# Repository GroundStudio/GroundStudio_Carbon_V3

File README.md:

GroundStudio Carbon V3
====================================

Get it from [ardushop.ro](https://ardushop.ro/en/electronics/537-placa-de-dezvoltare-carbon-v3-6427854000392.html)

Explore all the GroundStudio products at [ardushop.ro](https://ardushop.ro/en/37-groundstudio)

Description
-------------------
Features ESP32 based Pico V3-02 with 2.4 GHz WiFi, V4.2 Bluetooth, 8MB SPI Flash, 2MB SPI PSRAM, 520kB internal SRAM, 448kB ROM, 18 GPIO, 12 ADC and 6 touch sensitive pins, I²C 3V3 adapter, RGB smart LED, 1 cell LiPo/LiIon battery charger with optional battery connector and CH340C for USB comunication.

Contents
-------------------

* [/Documentation](https://github.com/GroundStudio/GroundStudio_Carbon_V3/tree/main/Documentation) -- Pinout.
* [/Hardware](https://github.com/GroundStudio/GroundStudio_Carbon_V3/tree/main/Hardware) -- Schematics, layout.
* [/Arduino](https://github.com/GroundStudio/GroundStudio_Carbon_V3/tree/main/Arduino/Examples) -- Arduino test examples.

Versions
-------------------
*(Not all tags shown)*

- [REV 0.0.2]:
  - testing different uart pins setup

- [REV 0.0.3]:
  - added test point for GPIO0
  - added 100nF in parallel with R14 for better battery voltage level reading
  - adjusted the position of pin labels for better visibility

License
-------------------

This is released under the [Attribution-ShareAlike 4.0 International (CC BY-SA 4.0)](https://creativecommons.org/licenses/by-sa/4.0/) license.
**You are welcome to use this for commercial purposes.**

Please consider contributing back to this project or others to help the open-source hardware community continue to thrive and grow!

Certifications:

[Open Source Hardware Association](https://certification.oshwa.org/ro000007.html)   
   
[
](https://certification.oshwa.org/ro000007.html)

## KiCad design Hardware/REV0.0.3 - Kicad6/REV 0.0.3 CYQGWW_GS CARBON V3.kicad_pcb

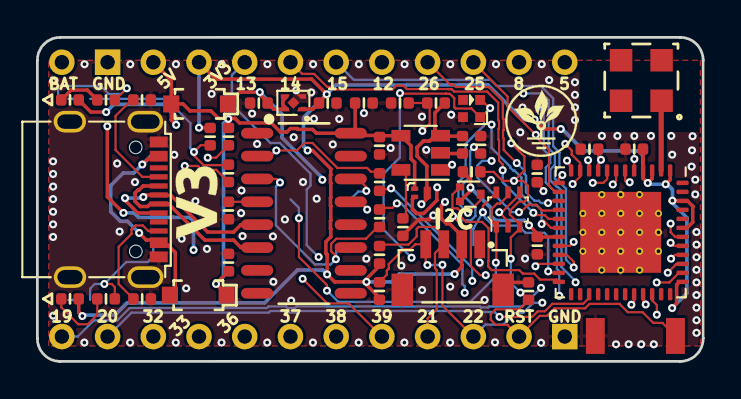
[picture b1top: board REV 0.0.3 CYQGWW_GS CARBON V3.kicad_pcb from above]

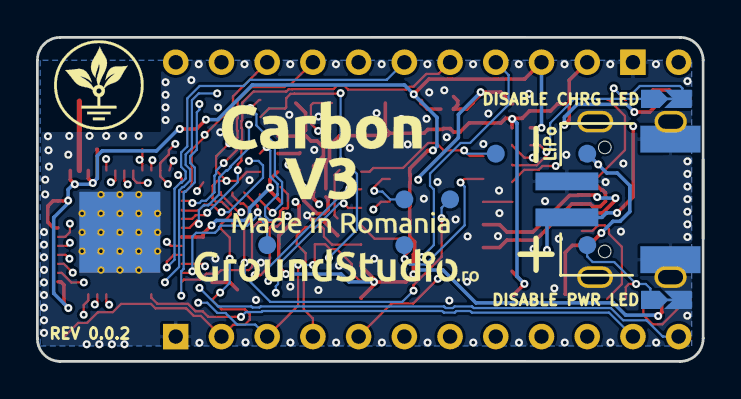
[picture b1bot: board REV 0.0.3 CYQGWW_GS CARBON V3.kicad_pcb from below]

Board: 4 copper layers, 37.0 x 18.0 mm, 56 parts (5 on the bottom side), 50 nets.

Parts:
ANT1: 2065130001
C1, C5, C6, C7, C11: C_0402_1uF_10V; C_0402_alt
C2, C9, C10: C_0402_100nF_16V; C_0402_alt
C3, C4: C_0402_10uF_10V; C_0402_alt
C8: C_0402_10nF_50V; C_0402_alt
CR1: SOD-123 B0520LW; SOD-123
D1: LED_0402_GREEN; LED_0402_alt
D3: SOD-123 B0520LW; SOD-123
IC1: SOT-23-5 BRCL4054CME; SOT-23-5
J1, J2: PinHeader_1x12_P2.54_V_M A2541WV-12P; PinHeader_1x12_P2.54mm_Vertical_Male
J4: PWR LED DISABLE; SolderJumper_NC
J7: disable CHARGING LED; SolderJumper_NC
LED2: LED_0402_RED; LED_0402_alt
LED3: SK6805-EC15 DY-S1515065; SK6805-EC15
Q1: SOT-363 MUN5214DW1T1G; SOT-363
Q2: SOT-883 LP0404N3T5G; SOT-883
R1, R2: R_0402_5.1k; R_0402_alt
R5: R_0402_100k; R_0402_alt
R6, R7, R16, R17: R_0402_3.3k; R_0402_alt
R8, R19: R_0402_2k; R_0402_alt
R9, R10, R11, R12: R_0402_1k; R_0402_alt
R13: R_0402_442k; R_0402_alt
R14: R_0402_160k; R_0402_alt
R15: R_0402_10k; R_0402_alt
R18: R_0402_820k; R_0402_alt
REG1: FBP1-1-4_ME6211C33U4AG-N; FBP1-1-4
SW1: TS342A2P-WZ
T1: SOT-723_DTA143ZMT2L; SOT-723
TP1: TP_RTS; TestPoint
TP2: IO0; TestPoint
TP3: TP_USB_VCC; TestPoint
TP5: TP_ONL; TestPoint
TP6: TP_TX; TestPoint
TP7: TP_RX; TestPoint
TP8: TP_DTR; TestPoint
U1: QFN-48-7x7mm ESP32-PICO-V3-02; QFN-48-1EP_7x7mm_P0.5mm_EP4.5x4.5mm
U2: SOP-16_150MIL CH340C; SOP-16_150MIL
USB1: USB_C 918-418K2023S40001; USB_C_C167321
X1: PH__1x02_P2.00mm_Horizontal C47647; PH__1x02_P2.00mm_Horizontal
X2: SH__1x04_Vertical C145961; SH__1x04_P1.00mm_Vertical

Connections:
+3V3: C2.1, C3.1, C6.1, J1.4, LED2.2, R15.2, R16.2, R17.1, R18.1, REG1.1, T1.2, U1.1, U1.3, U1.4, U1.19, U1.37, U1.43, U1.46, X2.2
+BAT: C4.1, IC1.3, J1.1, Q2.3, R13.2, X1.2
CH340C_RX: R12.2, TP7.~, U2.3
CH340C_TX: R11.2, TP6.~, U2.2
D+: U2.5, USB1.A6, USB1.B6
D-: U2.6, USB1.A7, USB1.B7
DTR: Q1.1, Q1.5, TP8.~, U2.13
EN: C1.1, C11.1, J2.11, Q1.3, R15.1, SW1.2, U1.9
GND: C1.2, C2.2, C3.2, C4.2, C5.1, C6.2, C7.2, C8.1, C9.2, C10.2, C11.2, IC1.2, J1.2, J2.12, J4.2, LED3.4, R1.2, R2.2, R5.1, R6.1, R8.1, R14.1, REG1.2, REG1.5, SW1.1, U1.49, U2.1, USB1.0, USB1.A1, USB1.A12, USB1.B1, USB1.B12, X1.0, X1.1, X2.0, X2.1
GPIO0: Q1.6, TP2.~, U1.23
GPIO2: LED3.1, U1.22
GPIO4: T1.1, U1.24
GPIO5: J1.12, U1.34
GPIO7: R7.1, R8.2, U1.32
GPIO8: J1.11, U1.33
GPIO12: J1.8, U1.18
GPIO13: J1.5, U1.20
GPIO14: J1.6, U1.17
GPIO15: J1.7, U1.21
GPIO19: J2.1, U1.38
GPIO20: J2.2, U1.27
GPIO21: J2.9, R16.1, U1.42, X2.3
GPIO22: J2.10, R17.2, U1.39, X2.4
GPIO25: J1.10, U1.14
GPIO26: J1.9, U1.15
GPIO27: R19.2, U1.16
GPIO32: J2.3, U1.12
GPIO33: J2.4, U1.13
unnamed: ANT1.1, U1.2
unnamed: C8.2, U2.4
unnamed: D1.1, R10.2
unnamed: IC1.5, R6.2
unnamed: J4.1, R9.2, TP5.~
unnamed: J7.2, R10.1
unnamed: LED2.1, R9.1
unnamed: LED3.2, T1.3
unnamed: R1.1, USB1.B5
unnamed: R2.1, USB1.A5
RTS: Q1.2, Q1.4, TP1.~, U2.14
RX_ESP32: R11.1, U1.40
SENS_CAPN: J2.7, U1.7
SENS_CAPP: J2.6, U1.6
SENS_VN: J2.8, U1.8
SENS_VP: J2.5, U1.5
TX_ESP32: R12.1, U1.41
USB: C7.1, C9.1, CR1.2, D1.2, D3.1, IC1.4, J1.3, Q2.1, R5.2, R7.2, U2.16
VBUS: C5.2, CR1.1, Q2.2, REG1.3, REG1.4
VBUS1*2: D3.2, TP3.~, USB1.A4, USB1.A9, USB1.B4, USB1.B9
VDET_2: C10.1, R13.1, R14.2, U1.11
~CHRG: IC1.1, J7.1, R18.2, R19.1, U1.10

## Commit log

2022-08-10 - initial commit
2022-08-26 - added schematic pdf file
2022-08-26 - added "Kicad6" to revision folder name
2022-10-07 - updated pinout to REV 2 - added arduino examples
2022-10-07 - changed baudrate to 9600
2022-12-21 - added example for reading battery level
2023-03-15 Update README.md
    - removed references to "library"
2023-07-07 Update HSPI_SD_card_test.ino
    fixed a typo on line 30 wich caused ESP32 to enter a boot loop.
2023-10-26 - added .step 3D file of the board
2023-10-30 - added datasheet
2023-12-07 - updated pinout and datasheet
2025-09-10 update shop links
